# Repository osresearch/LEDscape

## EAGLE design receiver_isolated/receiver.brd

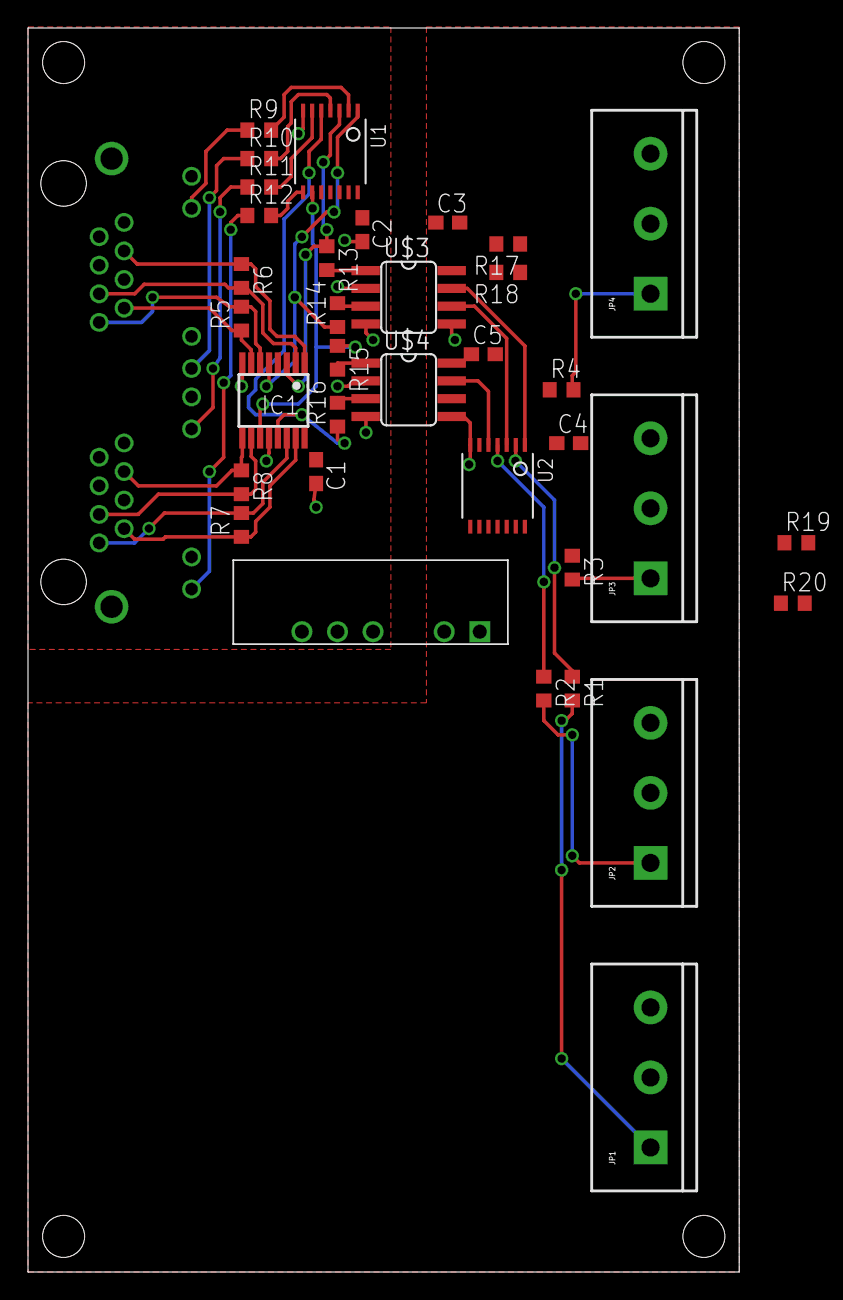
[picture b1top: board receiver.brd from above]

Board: 2 copper layers, 50.8 x 88.8 mm, 36 parts (0 on the bottom side), 40 nets.

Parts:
C1, C2, C3, C4, C5: .1uF; C0603
IC1: MAX3095CEE; QSOP16
JP1, JP2, JP3, JP4: SCREWTERMINAL-5MM-3
R1, R2, R3, R4: 100; R0603
R5, R6, R7, R8, R9, R10, R11, R12: 180; R0603
R13, R14, R15, R16, R17, R18, R19, R20: R0603
U1, U2: 74HC04_HEX_INVERTERTSSOP14; TSSOP14
U$1: RJ45_2X1
U$2: DC_DC_ISOLATED_0505; IB_XLS-1W
U$3, U$4: HCPL-0631-500E; SO08

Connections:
5V: C1.1, C2.1, IC1.4, IC1.16, U1.14, U$1.A_GREEN_+, U$1.A_YELLOW_+, U$1.B_GREEN_+, U$1.B_YELLOW_+, U$2.P$5
5V_IN: C3.1, C4.1, C5.1, JP1.2, JP2.2, JP3.2, JP4.2, R17.2, R18.2, R19.2, R20.2, U2.14, U$2.P$1, U$3.8, U$4.8
GND: C1.2, C2.2, IC1.8, IC1.12, U1.7, U$1.A_7, U$1.A_8, U$1.B_7, U$1.B_8, U$2.P$3, U$2.P$4, U$3.2, U$3.4, U$4.2, U$4.4
GND_IN: C3.2, C4.2, C5.2, JP1.3, JP2.3, JP3.3, JP4.3, U2.7, U$2.P$2, U$3.5, U$4.5
IND0: R9.2, U1.2
IND1: R10.2, U1.4
IND2: R11.2, U1.6
IND3: R12.2, U1.8
unnamed: JP1.1, R1.2
unnamed: IC1.6, R5.2, U$1.A_1
unnamed: IC1.7, R5.1, U$1.A_2
unnamed: JP2.1, R2.2
unnamed: JP3.1, R3.2
unnamed: JP4.1, R4.2
unnamed: R9.1, U$1.A_YELLOW_-
unnamed: IC1.2, R6.2, U$1.A_3
unnamed: IC1.1, R6.1, U$1.A_6
unnamed: IC1.14, R7.2, U$1.B_1
unnamed: IC1.15, R7.1, U$1.B_2
unnamed: IC1.10, R8.2, U$1.B_3
unnamed: IC1.9, R8.1, U$1.B_6
unnamed: R10.1, U$1.A_GREEN_-
unnamed: R11.1, U$1.B_YELLOW_-
unnamed: R12.1, U$1.B_GREEN_-
unnamed: R13.2, U$3.1
unnamed: R14.2, U$3.3
unnamed: R15.2, U$4.1
unnamed: R16.2, U$4.3
unnamed: R18.1, U2.3, U$3.6
unnamed: R17.1, U2.1, U$3.7
unnamed: R19.1, U2.5, U$4.7
unnamed: R20.1, U2.9, U$4.6
unnamed: R1.1, U2.2
unnamed: R2.1, U2.4
unnamed: R3.1, U2.6
unnamed: R4.1, U2.8
S0: IC1.5, R14.1, U1.1
S1: IC1.3, R13.1, U1.3
S2: IC1.13, R16.1, U1.5
S3: IC1.11, R15.1, U1.9

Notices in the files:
parts and their libraries:
SparkFun-Connectors: Licensing: CC v3.0 Share-Alike You are welcome to use this library for commercial purposes.
